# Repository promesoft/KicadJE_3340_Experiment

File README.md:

# AS3340/CEM3340 Experiment
AS3340 Experiments

# Vital Components
Based on http://www.alfarzpp.lv/eng/sc/AS3340.pdf

Sourced through https://syntaxis.com.pl/en/voltage-controlled-oscilators/8-as3340-vco.html

# Status - Delivered
## Initial 
| Stage  | Detail | Status |
| ------------- | ------------- | ------------- |
| create material  | sch | done |
| | pcb | done  |
| | gerber | done |
| production  |   | ok |
|  | produced | ok |
|  | delivered | ok |
## Preliminary validation
| Test  | Detail | Status |
| ------------- | ------------- | ------------- |
| Initial Inspection | Face | Looks good - nice alignment and finish |
| Initial Inspection | PCB | Several errors |
| Initial Technical Test |  | Several errors |
| Initial Product Test |  |  |

## Secondary validation
| Test  | Detail | Status |
| ------------- | ------------- |------------- |
| Product Test |  | |
| Quality | | |
| Long Term Product Test |  |  |
| Power Draw |  | 

## Errata
### Errata - 3340
 - Sync circuit messed up in SCH
 - Fine pot reversed
 - D103 D104 should go to GND and + 5V

## Issues and Notes
### 3340 Faceplate and PCB does not match for input jacks
### + 6V -1V CV

# Pictures

# Schematic
## AS3340 Data Sheet

## Prototype

Move from breadboard to stripboard as breadboard is not stable in any way.

Quick mods to get started
* 820R -> 680R (-12v)
* 470R -> 680R (CV in)
* 24k -> 20k (Rz tracking serial res)
* 1k8 -> 2k (Scale)
* 1M5 -> 1M (+12v pull up FM in)
* 5k6 -> 4k7 (scale adj RT)

Works ok for feature validation - but sync and PWM adjustment circuits should be included - as well as level adjustment.
Protection of the chip is also needed.
20K pot not needed.

# Inspiration
## AS3340 Data Sheet

http://www.alfarzpp.lv/eng/sc/AS3340.pdf

## CEM3340 Data Sheet - Via Electric Druid
CC BY-NC-SA 4.0

## CEM3340 Prophet 5 - Via Electric Druid
CC BY-NC-SA 4.0

https://electricdruid.net/cem3340-vco-voltage-controlled-oscillator-designs/

## CEM3340 Prophet T8 - Via Electric Druid
CC BY-NC-SA 4.0

https://electricdruid.net/cem3340-vco-voltage-controlled-oscillator-designs/

available under - https://creativecommons.org/licenses/by-nc-sa/4.0/

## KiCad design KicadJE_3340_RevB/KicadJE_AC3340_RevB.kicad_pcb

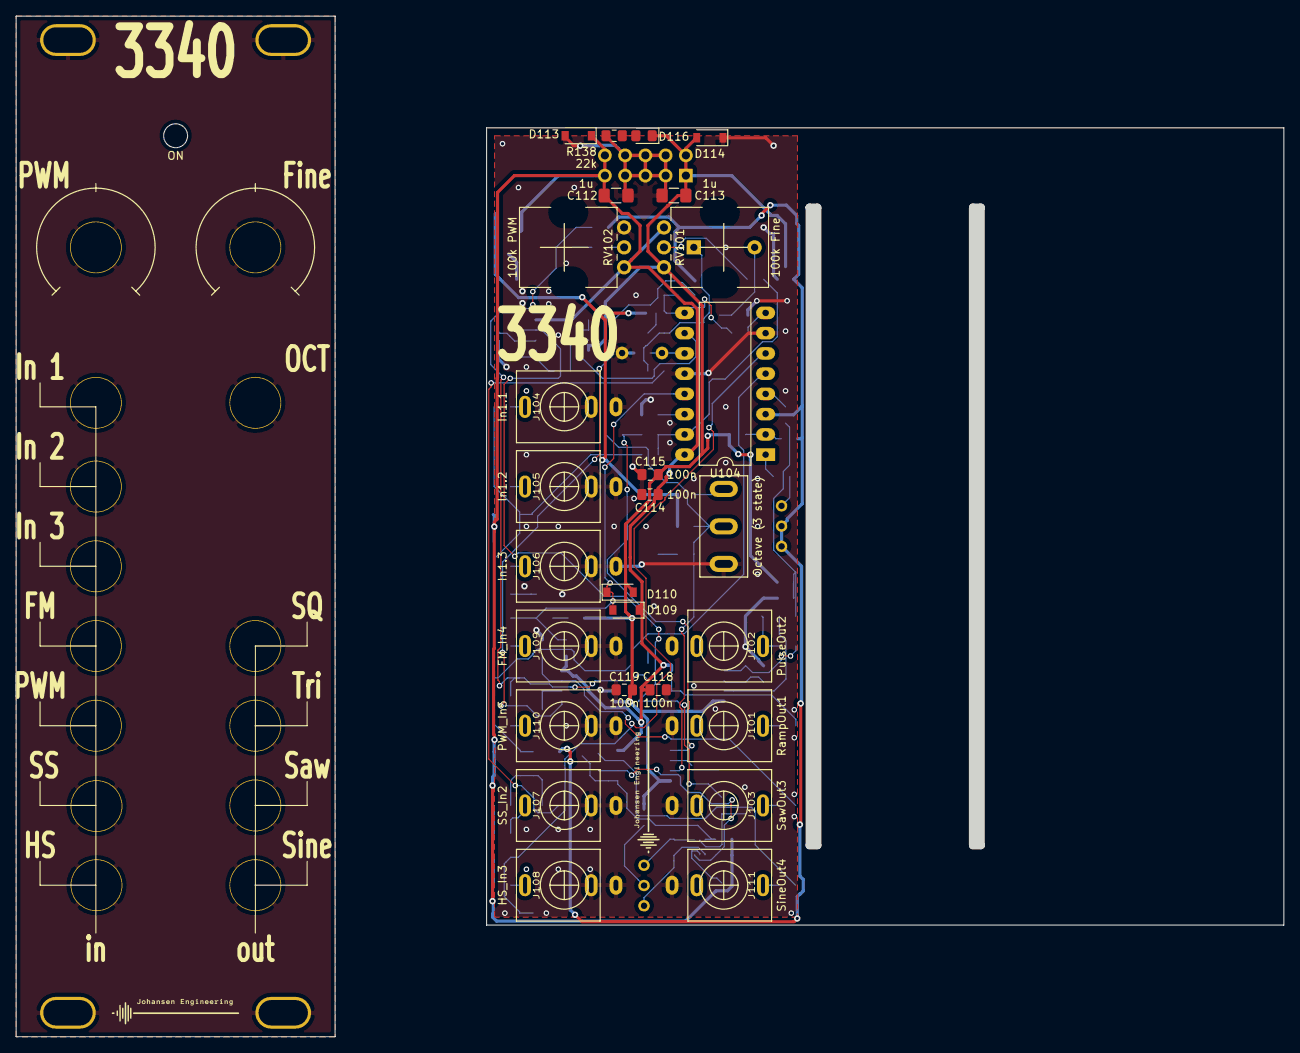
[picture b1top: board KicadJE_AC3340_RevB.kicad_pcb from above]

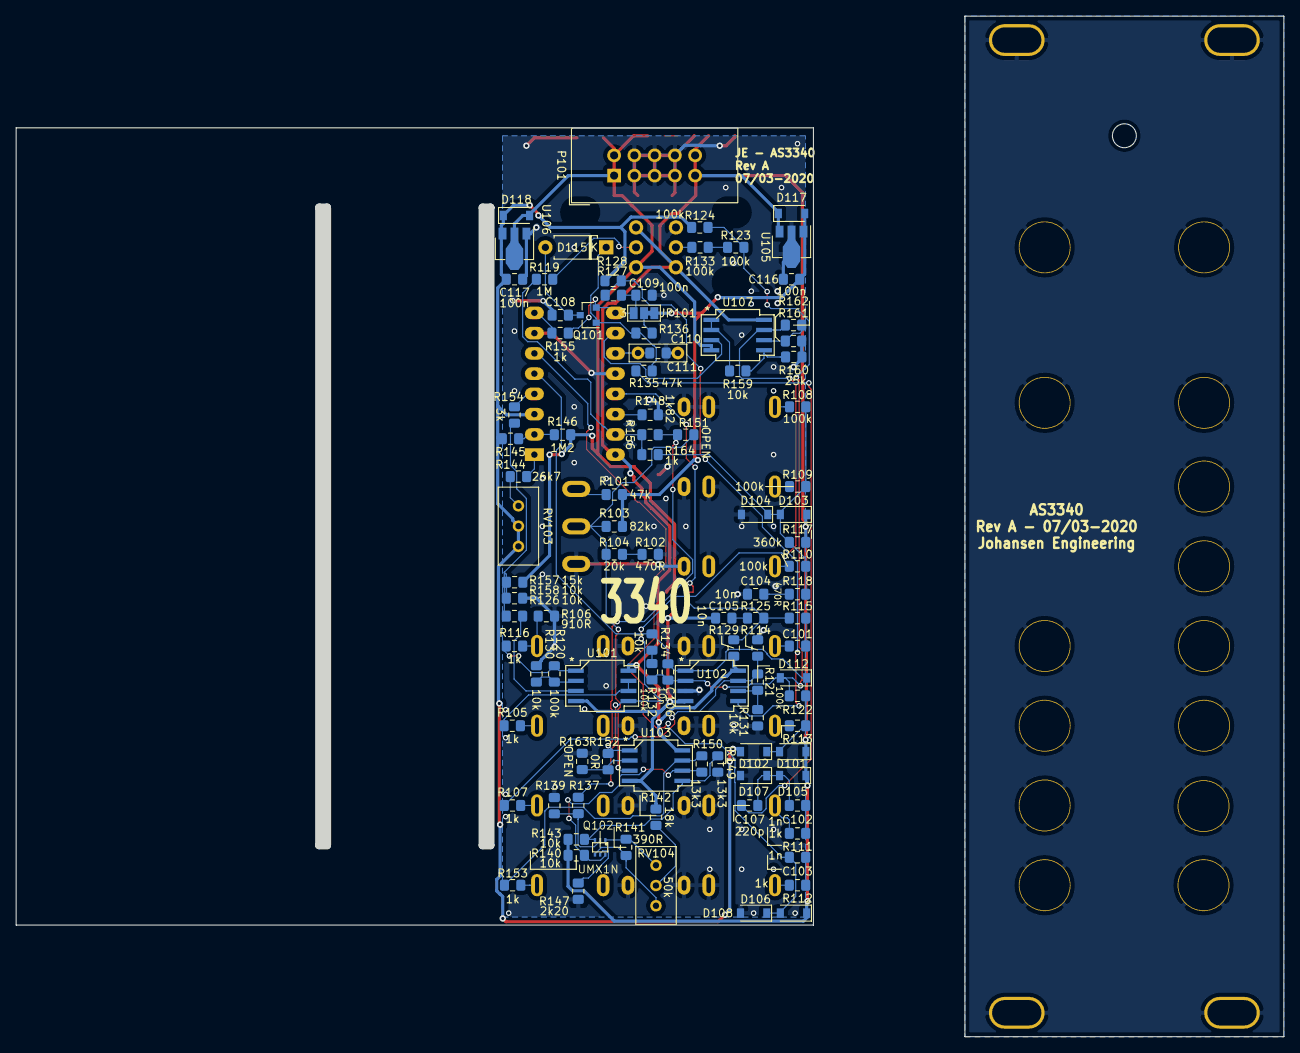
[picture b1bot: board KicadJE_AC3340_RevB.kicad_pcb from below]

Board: 2 copper layers, 100.0 x 100.0 mm, 146 parts (102 on the bottom side), 72 nets.

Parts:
C101, C108, C109, C114, C115, C116, C117, C118, C119: 100n; C_0805_2012Metric_Pad1.15x1.40mm_HandSolder
C102, C103: 1n; C_0805_2012Metric_Pad1.15x1.40mm_HandSolder
C104, C105, C106: 10n; C_0805_2012Metric_Pad1.15x1.40mm_HandSolder
C107: 220p; C_0805_2012Metric_Pad1.15x1.40mm_HandSolder
C110: 1n poly; C_Rect_L7.0mm_W2.0mm_P5.00mm
C111: 1n alt; C_0805_2012Metric_Pad1.15x1.40mm_HandSolder
C112, C113: 1u; C_1206_3216Metric_Pad1.42x1.75mm_HandSolder
D101, D102, D103, D104, D105, D106, D107, D108, D109, D110, D113, D114, D117, D118: 1N1007; D_SOD-123
D112: 1N4148; D_SOD-123
D115: Germanium; D_A-405_P7.62mm_Horizontal
D116: LED; LED_0805_2012Metric_Pad1.15x1.40mm_HandSolder
H101, H102, H103, H104: MountingHole_Pad; MountingHole_Eurorack3
H105: ON; LED_Hole_3mm
J101: RampOut1; PJ301SM
J102: PulseOut2; PJ301SM
J103: SawOut3; PJ301SM
J104: In1.1; PJ301SM
J105: In1.2; PJ301SM
J106: In1.3; PJ301SM
J107: SS_In2; PJ301SM
J108: HS_In3; PJ301SM
J109: FM_In4; PJ301SM
J110: PWM_In5; PJ301SM
J111: SineOut4; PJ301SM
JP101: Jumper; SolderJumper-3_P1.3mm_Bridged12_Pad1.0x1.5mm_NumberLabels
P101: HEADER_2x5_Doepfer; IDC-Header_2x05_P2.54mm_Vertical
Q101: MMBT3906; SOT-23
Q102: UMX1N; UMX1N_UMT6_DualNPN
R101, R135, R136, R137: 47k; R_0805_2012Metric_Pad1.15x1.40mm_HandSolder
R102, R118, R125: 470R; R_0805_2012Metric_Pad1.15x1.40mm_HandSolder
R103: 82k; R_0805_2012Metric_Pad1.15x1.40mm_HandSolder
R104: 20k; R_0805_2012Metric_Pad1.15x1.40mm_HandSolder
R105, R107, R111, R112, R113, R116, R153, R155, R164: 1k; R_0805_2012Metric_Pad1.15x1.40mm_HandSolder
R106: 910R; R_0805_2012Metric_Pad1.15x1.40mm_HandSolder
R108, R109, R110, R120, R122, R123, R124, R132, R133, R156: 100k; R_0805_2012Metric_Pad1.15x1.40mm_HandSolder
R114: 1k6; R_0805_2012Metric_Pad1.15x1.40mm_HandSolder
R115, R119: 1M; R_0805_2012Metric_Pad1.15x1.40mm_HandSolder
R117: 360k; R_0805_2012Metric_Pad1.15x1.40mm_HandSolder
R121, R128: 12k5; R_0805_2012Metric_Pad1.15x1.40mm_HandSolder
R126, R127, R130, R131, R134, R140, R143, R158, R159, R161: 10k; R_0805_2012Metric_Pad1.15x1.40mm_HandSolder
R129: 1M5; R_0805_2012Metric_Pad1.15x1.40mm_HandSolder
R138: 22k; R_0805_2012Metric_Pad1.15x1.40mm_HandSolder
R139, R147: 2k20; R_0805_2012Metric_Pad1.15x1.40mm_HandSolder
R141: 390R; R_0805_2012Metric_Pad1.15x1.40mm_HandSolder
R142: 18k; R_0805_2012Metric_Pad1.15x1.40mm_HandSolder
R144: 26k7; R_0805_2012Metric_Pad1.15x1.40mm_HandSolder
R145: 6k04; R_0805_2012Metric_Pad1.15x1.40mm_HandSolder
R146: 1M2; R_0805_2012Metric_Pad1.15x1.40mm_HandSolder
R148: 1k82; R_0805_2012Metric_Pad1.15x1.40mm_HandSolder
R149, R150: 13k3; R_0805_2012Metric_Pad1.15x1.40mm_HandSolder
R151, R163: OPEN; R_0805_2012Metric_Pad1.15x1.40mm_HandSolder
R152: 0R; R_0805_2012Metric_Pad1.15x1.40mm_HandSolder
R154: 3k; R_0805_2012Metric_Pad1.15x1.40mm_HandSolder
R157: 15k; R_0805_2012Metric_Pad1.15x1.40mm_HandSolder
R160, R162: 25k; R_0805_2012Metric_Pad1.15x1.40mm_HandSolder
RV101: 100k Fine; Potentiometer_China_RK09_Single_Vertical_AJ
RV102: 100k PWM; Potentiometer_China_RK09_Single_Vertical_AJ
RV103: 5k; Potentiometer_Bourns_3296W_Vertical
RV104: 50k; Potentiometer_Bourns_3296W_Vertical
SW101: Octave (3 state); SP1MS1
TP101: Oct; Pot_6m3
TP102: In1; Jack_6m3
TP103: In2; Jack_6m3
TP104: In3; Jack_6m3
TP105: SS; Jack_6m3
TP106: HS; Jack_6m3
TP107: FM; Jack_6m3
TP108: PWM; Jack_6m3
TP109: Tri; Jack_6m3
TP110: SQ; Jack_6m3
TP111: Saw; Jack_6m3
TP112: Fine; Pot_6m3_scale1
TP113: PWM; Pot_6m3_scale1
TP115: 3m5 jack; Jack_6m3
U101, U102, U103, U107: TL072; AJ_SO-8_5.3x6.2mm_P1.27mm
U104: AS3340; DIP-16_W10.16mm_LongPads
U105: L78L05_SOT89; SOT-89-3
U106: L79L05_SOT89; SOT-89-3

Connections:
3CVIn1: R119.2, R156.1, R164.1, U104.15
3FM_Lin_In4: D109.2, D110.1, R115.1, R125.2, R129.2, U104.13
3HardSyncIn3: C103.1, D106.2, D108.1, U104.6
3Octave: R103.1, R104.2, R151.2, SW101.2, U103.3
3PWM_Adj: R123.2, R133.2
3PWM_In5: C106.2, D112.1, R134.1, U102.1, U104.5
3Sine: J111.T, R153.1
3SoftSyncIn2: C102.1, C107.2, D105.2, D107.1
3VP_2: R126.1, R154.1, R157.2, R158.2
3VSO_3: C109.2, JP101.3, Q101.2, R127.1, R155.1, U104.9
3VTO_1: R137.2, R162.1, U101.5, U107.7
+5V: C116.2, D117.2, JP101.1, R101.2, R103.2, U105.1
+12VA: C112.1, C114.1, C118.1, D101.1, D103.1, D105.1, D106.1, D109.1, D113.1, D117.1, P101.9, P101.10, R117.2, R129.1, R140.2, R143.2, RV101.3, RV102.3, U101.8, U102.8, U103.8, U104.16, U105.3, U107.8
-5V: C117.2, D102.2, D118.1, R124.2, R128.1, R145.2, RV103.1, RV103.2, U104.3, U106.3
-12VA: C105.1, C113.2, C115.2, C119.2, D110.2, D114.2, D116.1, D118.2, P101.1, P101.2, R142.2, R146.2, R157.1, RV101.1, U101.4, U102.4, U103.4, U106.2, U107.4
GND: C104.1, C108.1, C109.1, C110.1, C111.2, C112.2, C113.1, C114.2, C115.1, C116.1, C117.1, C118.2, C119.1, D104.2, D107.2, D108.2, D113.2, D114.1, H101.1, H102.1, H103.1, H104.1, J101.S, J102.S, J103.S, J104.S, J104.TN, J105.S, J105.TN, J106.S, J106.TN, J107.S, J107.TN, J108.S, J108.TN, J109.S, J109.TN, J110.S, J110.TN, J111.S, P101.3, P101.4, P101.5, P101.6, P101.7, P101.8, R102.2, R106.1, R114.2, R130.1, R131.1, R138.2, R139.1, R147.1, R148.1, R149.2, R158.1, R160.1, R161.2, R163.2, RV102.1, SW101.1, TP101.1, TP102.1, TP103.1, TP104.1, TP105.1, TP106.1, TP107.1, TP108.1, TP109.1, TP110.1, TP111.1, TP112.1, TP113.1, TP115.1, U102.3, U104.7, U104.12, U105.2, U106.1
unnamed: C101.1, R115.2
unnamed: C101.2, J109.T
unnamed: C102.2, R111.1
unnamed: C103.2, R112.1
unnamed: C104.2, R118.1
unnamed: C105.2, R125.1
unnamed: C106.1, D112.2, R122.1, R123.1, R124.1, R132.2, U102.2
unnamed: C107.1, R135.2
unnamed: C108.2, D115.2, Q101.3
unnamed: C110.2, C111.1, U104.11
unnamed: D101.2, D102.1, R113.1, R122.2
unnamed: D103.2, D104.1, R108.1, R109.1, R110.1, R117.1, R118.2, R164.2
unnamed: D115.1, Q101.1, R135.1, R136.1
unnamed: D116.2, R138.1
unnamed: J101.T, R105.2
unnamed: J102.T, R106.2, R116.2
unnamed: J103.T, R107.2
unnamed: J104.T, R108.2
unnamed: J105.T, R109.2
unnamed: J106.T, R110.2
unnamed: J107.T, R111.2
unnamed: J108.T, R112.2
unnamed: J110.T, R113.2
unnamed: JP101.2, R136.2
unnamed: Q102.1, R141.2, RV104.1
unnamed: Q102.2, R137.1, R139.2
unnamed: Q102.3, R143.1, R149.1, U103.5
unnamed: Q102.4, R141.1, RV104.3
unnamed: Q102.5, R147.2
unnamed: Q102.6, R140.1, R150.1, U103.6
unnamed: R101.1, SW101.3
unnamed: R102.1, R104.1
unnamed: R105.1, U101.6, U101.7
unnamed: R107.1, R114.1, R121.2, U102.7
unnamed: R116.1, R120.2, U101.1
unnamed: R119.1, RV101.2
unnamed: R120.1, R130.2, U101.2
unnamed: R121.1, R131.2, U102.6
unnamed: R126.2, U101.3
unnamed: R127.2, R128.2, U102.5
unnamed: R132.1, R134.2
unnamed: R133.1, RV102.2
unnamed: R142.1, RV104.2
unnamed: R144.1, U104.1
unnamed: R144.2, RV103.3
unnamed: R145.1, R146.1, U104.2
unnamed: R148.2, U104.14
unnamed: R150.2, R153.2, U103.7
unnamed: R151.1, R152.1, R156.2, U103.1
unnamed: R152.2, R163.1, U103.2
unnamed: R154.2, U104.4
unnamed: R155.2, U104.8
unnamed: R159.1, R160.2, U107.5
unnamed: R159.2, U107.1, U107.2
unnamed: R161.1, R162.2, U107.6
unnamed: U104.10, U107.3

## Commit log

2020-02-17 Initial sch
2020-02-17 two sub sheets made ready
    incomplete
2020-02-17 Datasheet initial done sch
2020-02-17 protection initiated
    prophet circuit initiated
2020-02-17 pictures from electric druid
2020-02-19 Datasheet input protection
2020-02-29 AS3340 Diagram
2020-02-29 Learned from breadboard
2020-02-29 T8 coming alive
2020-02-29 AS 3340 JE initiated
2020-03-01 Octave switch JE
2020-03-01 cleaning up and migrating data sheet features
2020-03-01 Label JE 3 + Pot's
2020-03-05 Initial Diagram 3
2020-03-05 RevA
2020-03-05 Annotate
2020-03-05 base PCB
2020-03-05 DRC Done
2020-03-06 rev a
2020-03-07 Update KicadJE_AC3340_RevA.kicad_pcb
    Front Panel Guides
2020-03-07 Minor rearrangement
    remove 2 labels
2020-03-07 Update KicadJE_AC3340_RevA.kicad_pcb
    Faceplate labels
2020-03-07 Faceplate Gerber - Zip
2020-03-07 Mounting holes in schematic
    Prepare for next faceplate
2020-03-07 Create _saved_KicadJE_AC3340_RevA.sch
    With faceplate assignments
2020-03-07 LED hole
2020-03-07 TP -> mounting holes + ERC
2020-03-07 Faceplate A2
    change order of inputs
    move octave
    move led hole
2020-03-07 LED PWR moved
2020-03-07 main components placed
2020-03-07 fix in sine section
2020-03-08 Protection Diodes
2020-03-08 Update KicadJE_AC3340_RevA.kicad_pcb
    All Capacitors placed
2020-03-08 Update KicadJE_AC3340_RevA.kicad_pcb
    Initial routing
2020-03-08 Update KicadJE_AC3340_RevA.kicad_pcb
    DRC
2020-03-08 Labeled
2020-03-08 Gerber
2020-03-08 JLC order number
2020-03-10 Pictures
2020-03-10 naming
2020-04-07 RevB init
2020-04-08 Update KicadJE_AC3340_RevB.sch
    Fix misc errata from RevA - not complete
2021-05-06 Saved in newer kicad
2024-12-30 long time ago
